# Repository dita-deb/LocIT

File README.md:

# LocIT
Senior Design Project 2024  

## Overview  
LocIT, short for "Location Integrated Tracker," is a wearable safety device designed to enhance the security and monitoring of vulnerable individuals, such as children and elderly users. This project addresses real-world safety concerns with an innovative combination of hardware and software, offering real-time location tracking, facial recognition, geofencing, and more.

## Features  
- **GPS Location Tracking**: Accurate updates every 30 seconds with a 3-foot precision.
- **Temperature Monitoring**: Prevents device overheating by triggering shutdowns of non-essential components.
- **Vibrating Alerts**: Provides real-time notifications for geofence breaches or caregiver messages.
- **Gyroscope and Accelerometer**: Detects sudden movements or falls, notifying caregivers instantly.
- **Facial Recognition**: Identifies individuals near the wearer for added safety insights.
- **Geofencing**: Sends alerts when the user exits predefined safe zones.
- **Companion App**: Supports live tracking, notifications, and settings customization via FlutterFlow.

## Hardware System  
- **Sensors Subsystem**: Includes GPS, temperature, battery monitor, accelerometer, and gyroscope.
- **Actuators Subsystem**: Utilizes a vibration motor for silent notifications.
- **Communications Subsystem**: Transfers data securely via MQTT to AWS IoT Core and DynamoDB.
- **Power Subsystem**: Powered by a rechargeable LiPoly battery with over 24 hours of operation.
- **Central Processing Unit**: Raspberry Pi Zero 2 W for managing data, algorithms, and communication.

## Software System  
- Python-based main algorithm managing data collection, device state, and communication.
- AWS integration for real-time data storage and retrieval. [Backend-Webserver](https://02fydzyygd.execute-api.us-east-2.amazonaws.com/LocITDynamoDBDisplay)
- Companion app (FlutterFlow) for monitoring and control.

## Encasing Design  
- Constructed from PLA filament with 2 mm thickness for strength and durability.
- Compact dimensions: 2 inches wide, 4 inches long, and 2 inches deep.
- Three lid variations:
  - **No Slots Lid**: For fully enclosed design.
  - **4 Vents Lid**: Balanced ventilation and enclosure.
  - **9 Vents Lid**: Maximum cooling for high-temperature environments.

## Results  
- **High Accuracy**: GPS provides precise location tracking within a 3-foot radius.
- **Reliable Notifications**: Geofence breaches and fall detection alerts are delivered promptly.
- **Extended Usability**: Optimized power management ensures operation over a full day.

## Improvements and Optimizations  
Future enhancements include:
- Advanced facial recognition models for diverse conditions.
- Improved companion app usability with push notifications.
- Additional sensors for expanded functionality (e.g., heart rate monitoring).

## Getting Started  
Visit the [LocIT GitHub Repository](https://github.com/dita-deb/LocIT) for source code, hardware schematics, and additional documentation.

## License  
This project is licensed under a custom license. Redistribution, modification, or commercial use is restricted without explicit permission from the contributors. See the [LICENSE](LICENSE) file for more details.

## Contributors  
- **Anindita Deb** (dita-deb)  
- **Zachary Ponder** (ponder-zachary)  
- **Avery Porter** (Averyp119)
- **Damisi Kayode** (DamisiKayode0312)

## Acknowledgments  
Special thanks to Professor Jeffrey L. Yiin at Kennesaw State University for guidance and mentorship throughout the project.

---

*LocIT: Bringing peace of mind to caregivers while ensuring the safety of their loved ones.*

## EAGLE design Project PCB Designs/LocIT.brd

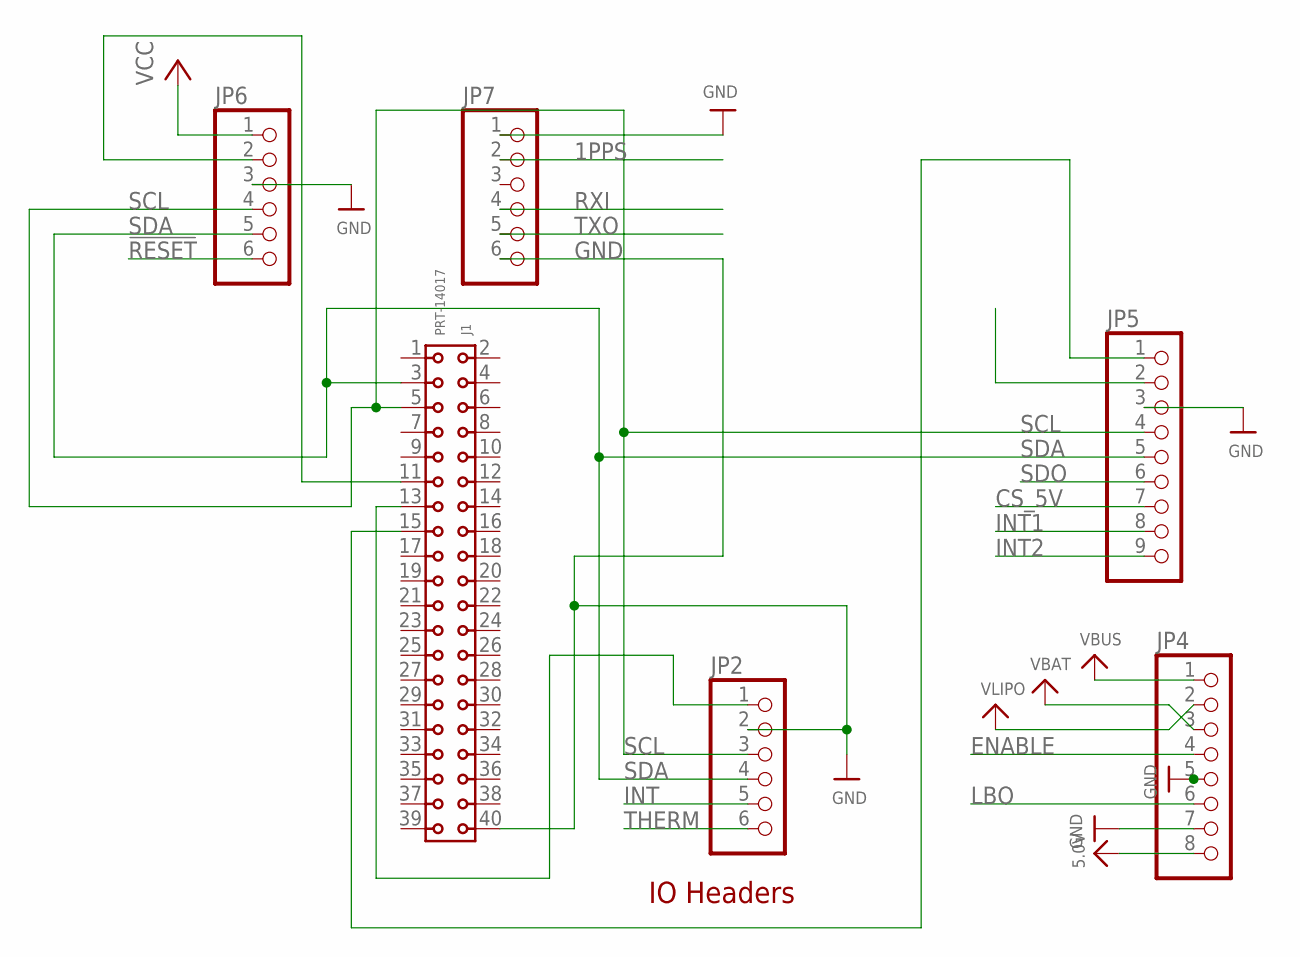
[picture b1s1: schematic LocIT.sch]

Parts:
J1: PRT-14017; 61304021821
JP2, JP6, JP7: HEADER-1X670MIL; 1X06_ROUND_70
JP4: HEADER-1X8ROUND; 1X08_ROUND
JP5: HEADER-1X970MIL; 1X09_ROUND_70

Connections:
1PPS: JP7.2
3.3V_GYRO: JP5.2
5.0V: JP4.8
!RESET: JP6.6
CS_5V: JP5.7
ENABLE: JP4.4
GND: J1.40, JP2.2, JP4.5, JP4.7, JP5.3, JP6.3, JP7.1, JP7.6
INT: JP2.5
INT1: JP5.8
INT2: JP5.9
LBO: JP4.6
unnamed: J1.11, JP6.2
RXI: JP7.4
SCL: J1.5, JP2.3, JP5.4, JP6.4
SDA: J1.3, JP2.4, JP5.5, JP6.5
SDO: JP5.6
THERM: JP2.6
TXO: JP7.5
VBAT: JP4.3
VBUS: JP4.1
VCC: JP6.1
VCC1: J1.13, JP2.1
VCC_GYRO: J1.15, JP5.1
VLIPO: JP4.2

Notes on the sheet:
IO Headers

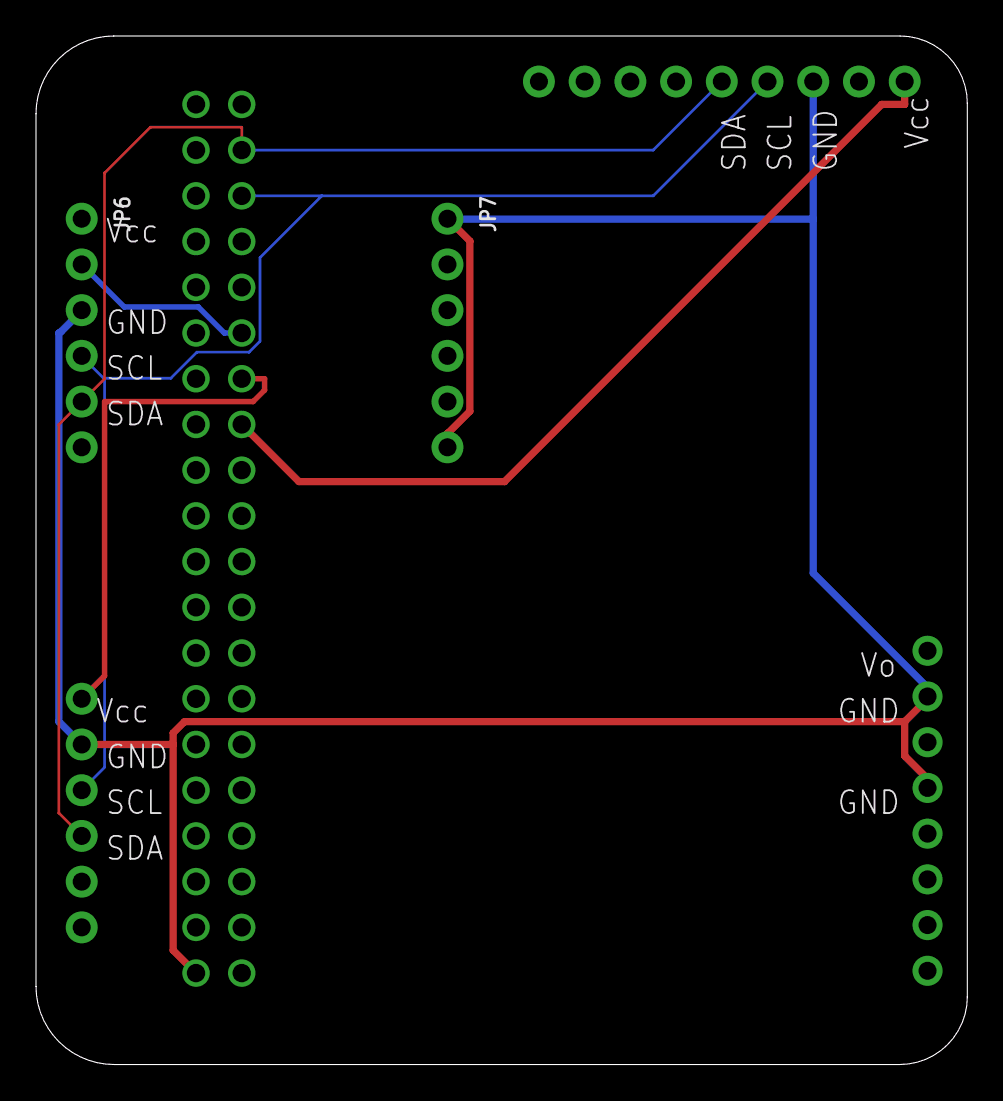
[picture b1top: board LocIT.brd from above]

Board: 2 copper layers, 51.7 x 57.1 mm, 6 parts (1 on the bottom side), 6 nets.

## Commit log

2024-04-16 Rename GPS Module/GPS_Tracker.ino to GPS Module/TinyCircuits-GPS-Tracker-Tutorial-master/GPS_Tracker.ino
2024-04-16 Rename GPS Module/SoftwareSerial256.cpp to GPS Module/TinyCircuits-GPS-Tracker-Tutorial-master/SoftwareSerial256.cpp
2024-04-16 Rename GPS Module/SoftwareSerial256.h to GPS Module/TinyCircuits-GPS-Tracker-Tutorial-master/SoftwareSerial256.h
2024-09-09 Rename MCP9808README.rst to MCP9808 Library Info.rst
2024-09-09 Create RaspberryPi
    This is the code that will be utilized for the GPS Tracker for the Raspberry Pi.
2024-09-09 Create Notification Alert Driver
2024-09-09 Create Alert Code
2024-09-09 Rename RaspberryPi to RaspberryPi.py
2024-09-09 Rename Alert Code to AlertCode.py
2024-09-16 Rename 3D Renders/Part Studio 1 (1).png to 3D Renders/Proposal/Part Studio 1 (1).png
2024-09-16 Rename 3D Renders/Part Studio 1 (3)_1.png to 3D Renders/Proposal/Part Studio 1 (3)_1.png
2024-09-16 Rename 3D Renders/Part Studio 1 (4)_1.png to 3D Renders/Proposal/Part Studio 1 (4)_1.png
2024-09-16 Rename 3D Renders/Part Studio 1 (5)_1.png to 3D Renders/Proposal/Part Studio 1 (5)_1.png
2024-09-16 Rename 3D Renders/Part Studio 1 (6).png to 3D Renders/Proposal/Part Studio 1 (6).png
2024-09-16 Rename 3D Renders/compasscam.jpg to 3D Renders/Proposal/compasscam.jpg
2024-09-16 Rename 3D Renders/doorwatchernecklace.jpg to 3D Renders/Proposal/doorwatchernecklace.jpg
2024-09-16 Rename 3D Renders/ringnecklace.jpg to 3D Renders/Proposal/ringnecklace.jpg
2024-09-16 Rename Camera Module/Camera Set Up/FacialExpressions.txt to Camera Module/Proposal/Camera Set Up/FacialExpressions.txt
2024-09-16 Rename Camera Module/Camera Set Up/OpenCV_install.txt to Camera Module/Proposal/Camera Set Up/OpenCV_install.txt
2024-09-16 Rename Camera Module/camera_calibration/pattern.png to Camera Module/Proposal/camera_calibration/pattern.png
2024-09-16 Rename Camera Module/docs/5Mohl.jpg to Camera Module/Proposal/docs/5Mohl.jpg
2024-09-16 changed folder to Proposal
2024-09-21 Update README.md
    Updated readme description for each file
2024-09-30 Add files via upload
    STL file of the first 3D printed prototype, consists of the body and a cover
2024-09-30 Delete Camera Module/Facial_Recognition_PC/names.json
    not necessary for the main files to work (just how names are saved as lists are implemented in this file)
2024-09-30 Create App Development\
2024-09-30 Create ui and ux
2024-09-30 Add files via upload
    Overview of the current UI/UX app for the LocIT app.
2024-09-30 Create Flutterflow App Preview Link
    Heres the link to preview the current app in Flutterflow
2024-10-07 Rename Flutterflow App Preview Link to Flutterflow App Preview Link .txt
2024-10-07 Rename Flutterflow App Preview Link .txt to Flutterflow App Preview Link .doc
2024-10-07 Rename Flutterflow App Preview Link .doc to Flutterflow App Preview Link .pdf
2024-10-07 Rename Flutterflow App Preview Link .pdf to Flutterflow App Preview Link .docx
2024-10-07 Rename Flutterflow App Preview Link .docx to Flutterflow App Preview Link
2024-10-07 changed directories
2024-10-23 Create BatteryAWS.py
    First attempt at the battery AWS with lowBattery.
2024-11-06 added video folder and added videos
2024-11-06 update files for pi camera
2024-11-06 face_recognizer.py file added
2024-11-06 face_train.py file added
2024-11-06 Update main.py
    Working alert notification system and data to DynamoDB table.
2024-11-06 Added additional notes of change
2024-11-21 added folders and new stl files for milestone 3
2024-11-21 Create HardwareBlockDiagram
2024-11-21 Rename HardwareBlockDiagram to HardwareBlockDiagram.txt
2024-11-23 main.py
2024-12-09 renamed
2024-12-10 Create LICENSE
2024-12-10 Update LICENSE

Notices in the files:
parts and their libraries:
microbuilder: This work is placed in the public domain, and may be freely used for commercial and non-commercial work with the following conditions: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
